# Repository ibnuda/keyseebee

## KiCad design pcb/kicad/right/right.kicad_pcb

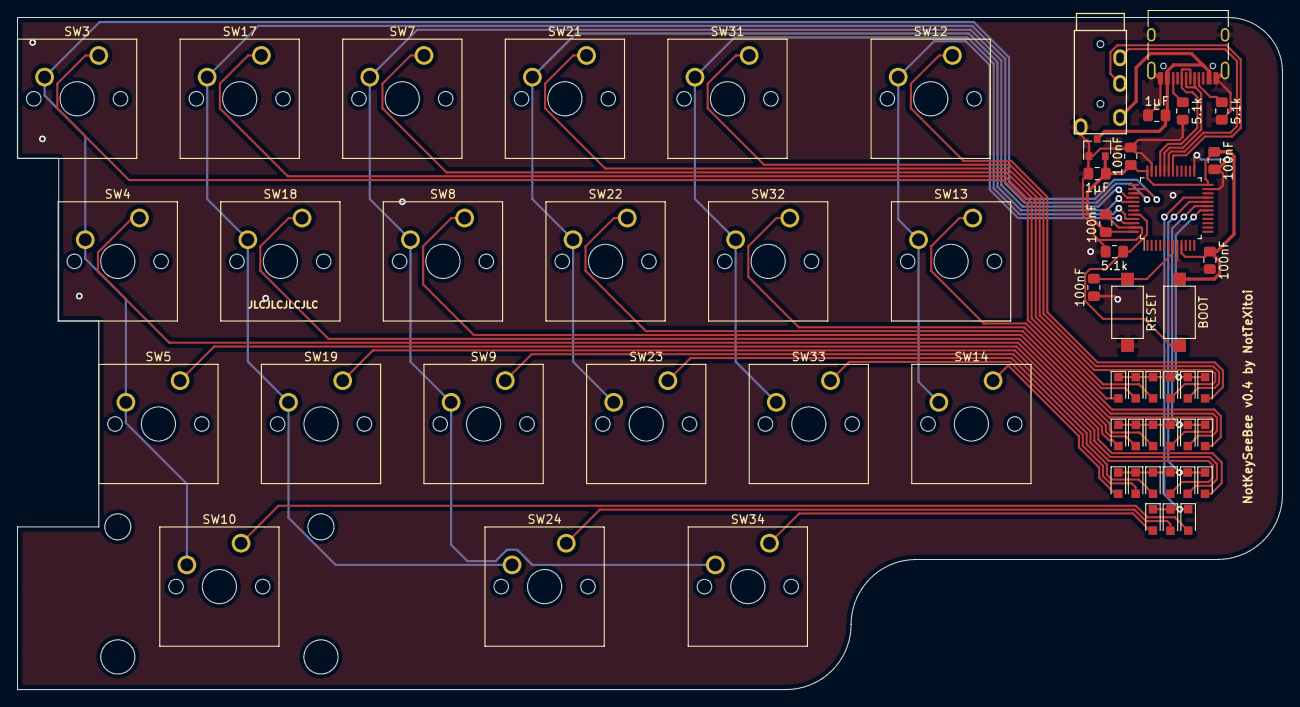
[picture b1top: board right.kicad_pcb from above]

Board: 2 copper layers, 148.2 x 78.7 mm, 58 parts (0 on the bottom side), 42 nets.

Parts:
C1, C2, C3, C4, C5: 100nF; C_0805_2012Metric_Pad1.15x1.40mm_HandSolder
C6, C7: 1µF; C_0805_2012Metric_Pad1.15x1.40mm_HandSolder
D5: D1.1; D_SOD-323_HandSoldering
D6: D2.1; D_SOD-323_HandSoldering
D7: D3.1; D_SOD-323_HandSoldering
D9: D1.3; D_SOD-323_HandSoldering
D10: D2.3; D_SOD-323_HandSoldering
D11: D3.3; D_SOD-323_HandSoldering
D12: D4.3; D_SOD-323_HandSoldering
D14: D1.6; D_SOD-323_HandSoldering
D15: D2.6; D_SOD-323_HandSoldering
D16: D3.6; D_SOD-323_HandSoldering
D19: D1.2; D_SOD-323_HandSoldering
D20: D2.2; D_SOD-323_HandSoldering
D21: D3.2; D_SOD-323_HandSoldering
D23: D1.4; D_SOD-323_HandSoldering
D24: D2.4; D_SOD-323_HandSoldering
D25: D3.4; D_SOD-323_HandSoldering
D26: D4.4; D_SOD-323_HandSoldering
D33: D1.5; D_SOD-323_HandSoldering
D34: D2.5; D_SOD-323_HandSoldering
D35: D3.5; D_SOD-323_HandSoldering
D36: D4.5; D_SOD-323_HandSoldering
J1: USB_C_Receptacle_USB2.0; USB_C_Receptacle_HRO_TYPE-C-31-M-12
J2: AudioJack4; TRRS-PJ-320A-no-Fmask
R1, R6, R7: 5.1k; R_0805_2012Metric_Pad1.15x1.40mm_HandSolder
SW1: BOOT; SW_SPST_CK_RS282G05A3
SW2: RESET; SW_SPST_CK_RS282G05A3
SW3, SW4, SW5, SW7, SW8, SW9, SW14, SW17, SW18, SW19, SW21, SW22, SW23, SW31, SW32, SW33: SW_Push; SW_Cherry_MX_1.00u_PCB
SW10: SW_Push; SW_Cherry_MX_2.75u_PCB
SW12: SW_Push; SW_Cherry_MX_1.50u_PCB
SW13, SW24, SW34: SW_Push; SW_Cherry_MX_1.25u_PCB
U1: STM32; LQFP-48_7x7mm_P0.5mm
U2: LDO; SOT-23

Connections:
3.3V: C2.2, C3.2, C4.2, C5.2, C6.2, SW1.2, U1.9, U1.24, U1.36, U1.48, U2.2
5V: C7.2, J1.A4, J1.A9, J1.B4, J1.B9, J2.2, U2.3
COL1: SW12.2, SW13.2, SW14.2, U1.46
COL2: SW31.2, SW32.2, SW33.2, U1.45
COL3: SW21.2, SW22.2, SW23.2, U1.41
COL4: SW7.2, SW8.2, SW9.2, SW34.2, U1.40
COL5: SW17.2, SW18.2, SW19.2, SW24.2, U1.39
COL6: SW3.2, SW4.2, SW5.2, SW10.2, U1.38
D+: J1.A6, J1.B6, U1.33
D-: J1.A7, J1.B7, U1.32
GND: C1.1, C2.1, C3.1, C4.1, C5.1, C6.1, C7.1, J1.A1, J1.A12, J1.B1, J1.B12, J1.S1, J2.1, R1.2, R6.2, R7.2, SW2.1, U1.8, U1.23, U1.25, U1.35, U1.47, U2.1
unnamed: C1.2, SW2.2, U1.7
unnamed: D5.2, SW3.1
unnamed: D6.2, SW4.1
unnamed: D7.2, SW5.1
unnamed: D9.2, SW7.1
unnamed: D10.2, SW8.1
unnamed: D11.2, SW9.1
unnamed: D12.2, SW10.1
unnamed: D14.2, SW12.1
unnamed: D15.2, SW13.1
unnamed: D16.2, SW14.1
unnamed: D19.2, SW17.1
unnamed: D20.2, SW18.1
unnamed: D21.2, SW19.1
unnamed: D23.2, SW21.1
unnamed: D24.2, SW22.1
unnamed: D25.2, SW23.1
unnamed: D26.2, SW24.1
unnamed: D33.2, SW31.1
unnamed: D34.2, SW32.1
unnamed: D35.2, SW33.1
unnamed: D36.2, SW34.1
unnamed: J1.A5, R7.1
unnamed: J1.B5, R6.1
unnamed: R1.1, SW1.1, U1.44
ROW1: D5.1, D9.1, D14.1, D19.1, D23.1, D33.1, U1.18
ROW2: D6.1, D10.1, D15.1, D20.1, D24.1, D34.1, U1.19
ROW3: D7.1, D11.1, D16.1, D21.1, D25.1, D35.1, U1.20
ROW4: D12.1, D26.1, D36.1, U1.21
RX: J2.4, U1.31
TX: J2.3, U1.30

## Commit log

2020-12-16 yeet.
